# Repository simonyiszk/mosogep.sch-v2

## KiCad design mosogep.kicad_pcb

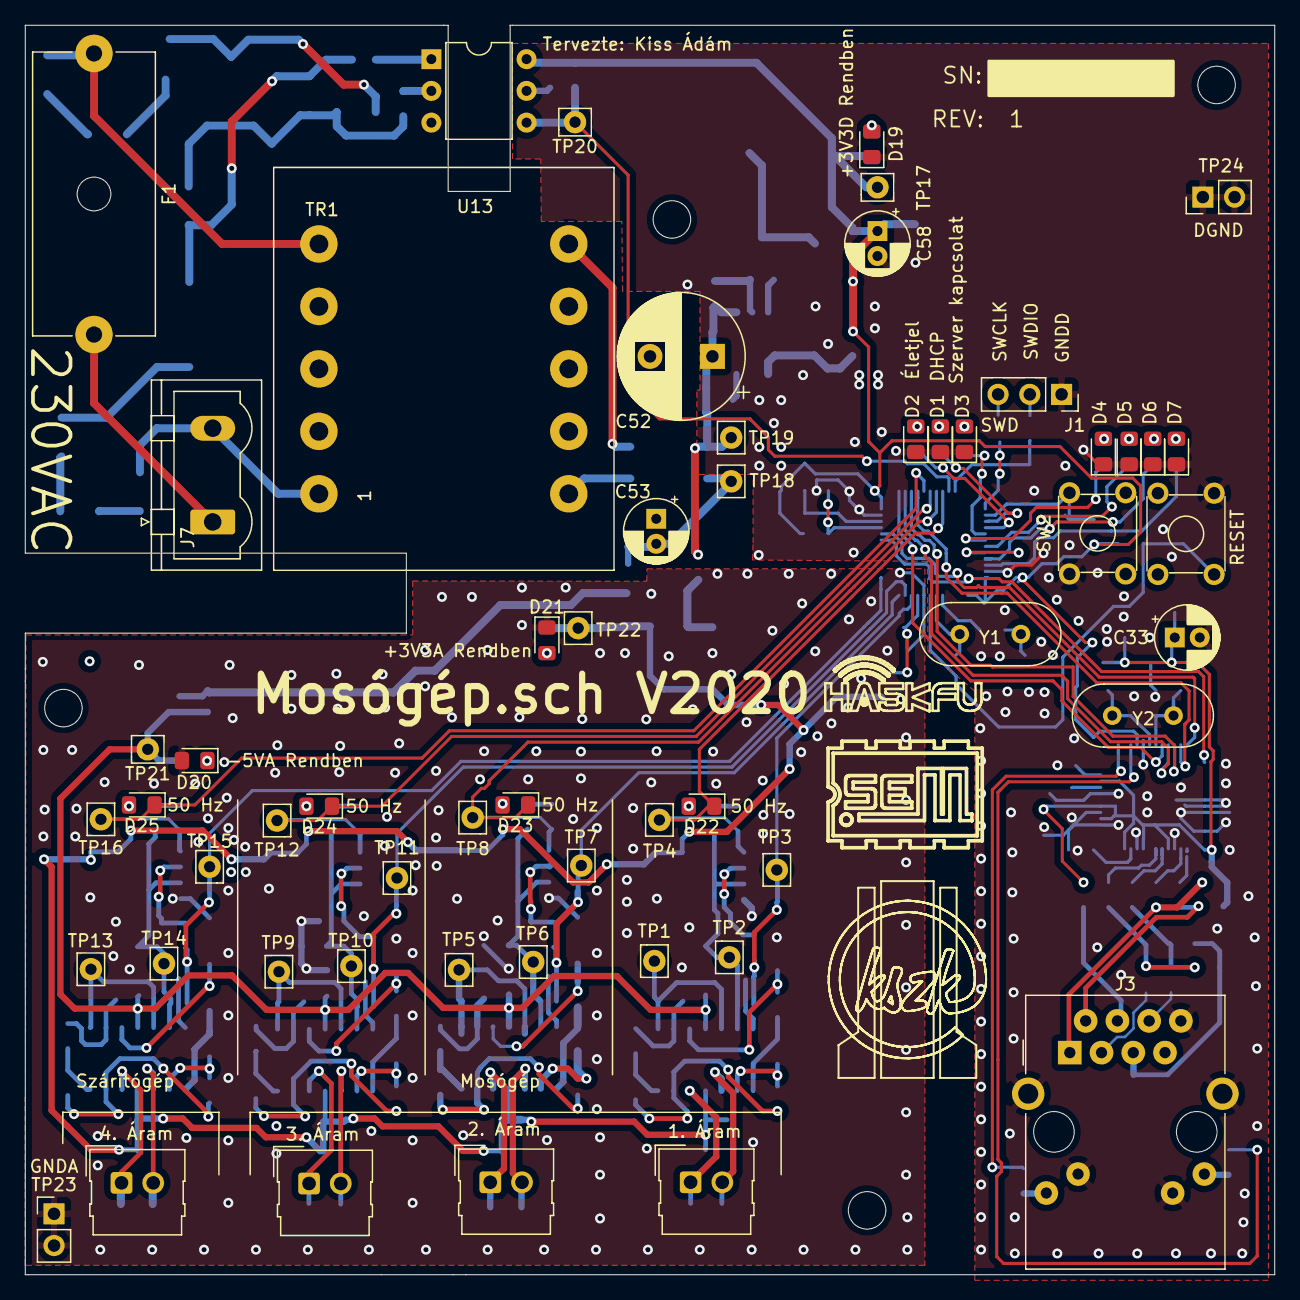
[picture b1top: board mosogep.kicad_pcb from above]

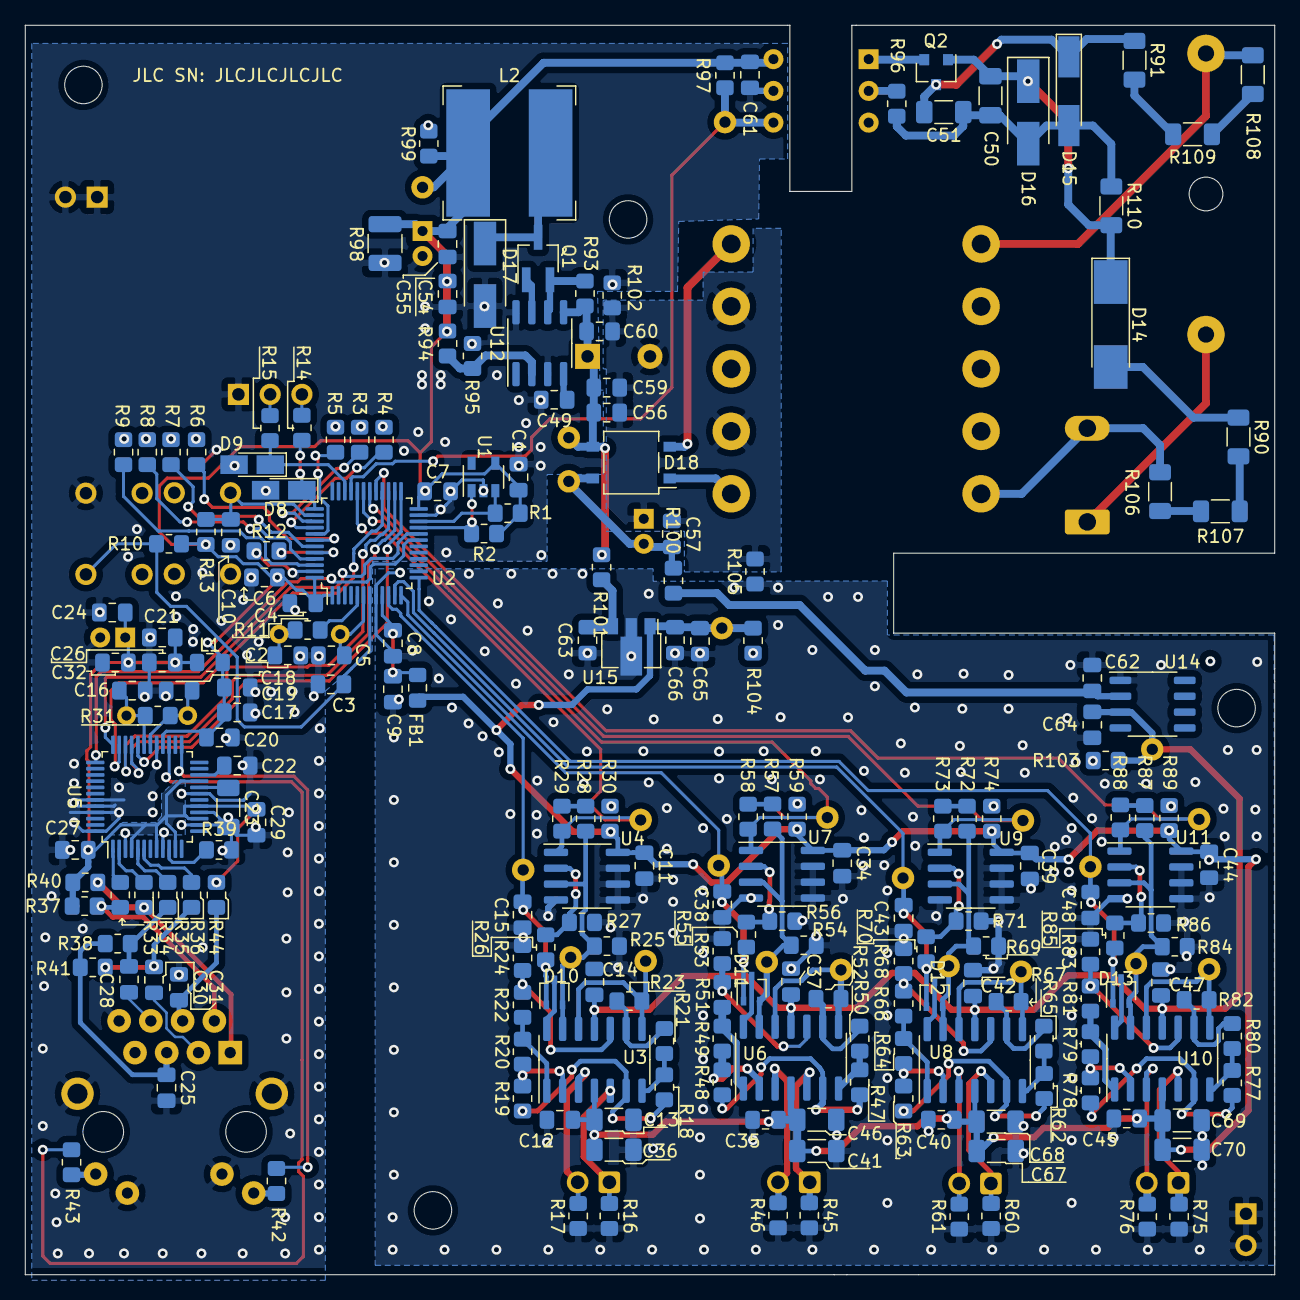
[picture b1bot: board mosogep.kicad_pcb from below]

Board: 2 copper layers, 100.0 x 100.0 mm, 264 parts (204 on the bottom side), 153 nets.

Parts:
C1, C4, C6, C7, C8, C11, C12, C14, C17, C19, C20, C21, C24, C26, C27, C29, C32, C34, C35, C37, C39, C40, C42, C44, C45, C47, C49, C54, C56, C57, C59, C60, C61, C62, C63: 100n; C_0805_2012Metric_Pad1.18x1.45mm_HandSolder
C2, C5: 20p; C_0805_2012Metric_Pad1.18x1.45mm_HandSolder
C3, C9, C10, C22, C25, C55, C65, C66: 10n; C_0805_2012Metric_Pad1.18x1.45mm_HandSolder
C13, C23, C36, C41, C46, C67, C68, C69, C70: 4u7; C_1206_3216Metric_Pad1.33x1.80mm_HandSolder
C15, C38, C43, C48: 1u; C_0805_2012Metric_Pad1.18x1.45mm_HandSolder
C16, C18: 18p; C_0805_2012Metric_Pad1.18x1.45mm_HandSolder
C28, C30: 6n8; C_0805_2012Metric_Pad1.18x1.45mm_HandSolder
C31: 22n; C_0805_2012Metric_Pad1.18x1.45mm_HandSolder
C33: 10u; CP_Radial_D5.0mm_P2.00mm
C50: 560p; C_1206_3216Metric_Pad1.33x1.80mm_HandSolder
C51: 330n; C_1206_3216Metric_Pad1.33x1.80mm_HandSolder
C52: 1000u; CP_Radial_D10.0mm_P5.00mm
C53: 100u; CP_Radial_D5.0mm_P2.00mm
C58: 47u low esr; CP_Radial_D5.0mm_P2.00mm
C64: C; C_0805_2012Metric_Pad1.18x1.45mm_HandSolder
D1, D2, D3, D4, D5, D6, D7, D19, D20, D21, D22, D23, D24, D25: LED; LED_0805_2012Metric_Pad1.15x1.40mm_HandSolder
D8, D9: PGB1010603MR; D_MicroMELF_Handsoldering
D10, D11, D12, D13: BAT54AW; SOT-323_SC-70
D14: bzd27c100; D_MELF_Handsoldering
D15: 5V6; D_MiniMELF_Handsoldering
D16: ll4148; D_SMA_Handsoldering
D17: ss14; D_SMA_Handsoldering
D18: MB6S; TO-269AA
F1: 100mA; Fuseholder_Cylinder-5x20mm_Schurter_0031_8201_Horizontal_Op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
FB1: HF70ACC575032-TL; L_0805_2012Metric_Pad1.15x1.40mm_HandSolder
H1, H2, H3, H4: MountingHole; MountingHole_3mm
J1: Programozó csati; PinSocket_1x03_P2.54mm_Vertical
J2, J4, J5, J6: AC1010; Molex_SL_171971-0002_1x02_P2.54mm_Vertical
J3: RB1-1D6B8K1A; RJ45_Amphenol_RJMG1BD3B8K1ANR
J7: line_in; PhoenixContact_GMSTBVA_2,5_2-G_1x02_P7.50mm_Vertical
L1: HF70ACC575032-TL; L_0805_2012Metric_Pad1.15x1.40mm_HandSolder
L2: 93-03-18; L_Bourns-SRN1060
Q1: yjl2301c; SOT-23W_Handsoldering
Q2: BC817; SOT-23
R1, R2, R10, R12, R13, R30, R37, R40, R59, R74, R89: 10k; R_0805_2012Metric_Pad1.20x1.40mm_HandSolder
R3, R4, R5, R6, R7, R8, R9, R42, R43, R99: 330; R_0805_2012Metric_Pad1.20x1.40mm_HandSolder
R11: 470; R_0805_2012Metric_Pad1.20x1.40mm_HandSolder
R14, R15, R44, R100, R101: 10; R_0805_2012Metric_Pad1.20x1.40mm_HandSolder
R16, R17, R38, R41, R45, R46, R60, R61, R75, R76: 50; R_0805_2012Metric_Pad1.20x1.40mm_HandSolder
R18, R20, R23, R24, R25, R47, R49, R52, R53, R54, R62, R64, R67, R68, R69, R77, R79, R82, R83, R84: 100k; R_0805_2012Metric_Pad1.20x1.40mm_HandSolder
R19, R21, R22, R48, R50, R51, R63, R65, R66, R78, R80, R81: 200k; R_0805_2012Metric_Pad1.20x1.40mm_HandSolder
R26, R27, R55, R56, R70, R71, R85, R86: 50k; R_0805_2012Metric_Pad1.20x1.40mm_HandSolder
R28, R29, R31, R57, R58, R72, R73, R87, R88: 1M; R_0805_2012Metric_Pad1.20x1.40mm_HandSolder
R33, R34, R35, R36, R93, R102, R105: 0; R_0805_2012Metric_Pad1.20x1.40mm_HandSolder
R39: 12.4k 1%; R_0805_2012Metric_Pad1.20x1.40mm_HandSolder
R90, R91, R106, R107, R108, R109: 82k; R_1206_3216Metric_Pad1.30x1.75mm_HandSolder
R94, R95, R103, R104: R; R_0805_2012Metric_Pad1.20x1.40mm_HandSolder
R96: 220; R_0805_2012Metric_Pad1.20x1.40mm_HandSolder
R97: 1k; R_0805_2012Metric_Pad1.20x1.40mm_HandSolder
R98: műterhelés; R_1210_3225Metric_Pad1.30x2.65mm_HandSolder
R110: 470k; R_1206_3216Metric_Pad1.30x1.75mm_HandSolder
SW1, SW2: SW_DIP_x01; SW_TH_Tactile_Omron_B3F-10xx
TP1, TP2, TP3, TP4, TP5, TP6, TP7, TP8, TP9, TP10, TP11, TP12, TP13, TP14, TP15, TP16, TP17, TP18, TP19, TP20, TP21, TP22: TestPoint; Pin_D0.9mm_L10.0mm_W2.4mm_FlatFork
TP23, TP24: TestPoint_2Pole; PinHeader_1x02_P2.54mm_Vertical
TR1: TEZ2.0-D-2; Transformer_CHK_EI30-2VA_Neutral
U1: 24AA02-OT; SOT-23-5
U2: STM32F030C6Tx; LQFP-48_7x7mm_P0.5mm
U3, U6, U8, U10: mc33204; SOIC-14_3.9x8.7mm_P1.27mm
U4, U7, U9, U11: LM393; SOIC-8_3.9x4.9mm_P1.27mm
U5: W5500; LQFP-48_7x7mm_P0.5mm
U12: max1649; SOIC-8_3.9x4.9mm_P1.27mm
U13: H11L1; DIP-6_W7.62mm
U14: L79L05_SOT89; SO-8_3.9x4.9mm_P1.27mm
U15: L78L33_SOT89; SOT-89-3
Y1: 8MHz; Crystal_HC18-U_Vertical
Y2: 25MHz; Crystal_HC18-U_Vertical

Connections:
0: C52.2, C53.1, C56.2, C57.1, C59.2, C60.2, R102.2, R105.2, TR1.7, TR1.9
+3.3VA: C11.1, C12.1, C13.1, C34.1, C35.1, C36.1, C39.1, C40.1, C41.1, C44.1, C45.1, C46.1, C65.1, C66.1, C67.1, C68.1, C69.1, C70.1, FB1.2, R30.1, R59.1, R74.1, R89.1, R104.1, TP22.1, U3.4, U4.8, U6.4, U7.8, U8.4, U9.8, U10.4, U11.8, U15.1
+3V3: C1.1, C4.1, C6.1, C7.1, C17.1, C19.1, C20.1, C54.1, C55.1, C58.1, C61.1, L1.2, L2.1, R1.1, R2.1, R10.1, R13.1, R94.1, R97.1, R98.1, R99.1, TP17.1, U1.4, U2.1, U2.24, U2.48, U5.28, U13.6
-3V3: C14.1, C37.1, C42.1, C47.1, C64.2, R103.2, TP21.1, U3.11, U6.11, U8.11, U10.11, U14.3
/ETH_INT: U2.20, U5.36
/I2C_CLK: R2.2, U1.1, U2.21
/I2C_DAT: R1.2, U1.3, U2.22
/MISO: U2.27, U5.34
/MOSI: U2.28, U5.35
/SCLK: U2.26, U5.33
/aram1: C15.1, D10.1, R26.1, TP3.1, U2.10
/aram2: C38.1, D11.1, R55.1, TP7.1, U2.12
/aram3: C43.1, D12.1, R70.1, TP11.1, U2.11
/aram4: C48.1, D13.1, R85.1, TP15.1, U2.13
/fazis_referencia: R97.2, TP20.1, U2.33, U13.4
/fazisdetektor1: D22.1, R29.1, TP4.1, U2.32, U4.1
/fazisdetektor2: D23.1, R58.1, TP8.1, U2.31, U7.1
/fazisdetektor3: D24.1, R73.1, TP12.1, U2.30, U9.1
/fazisdetektor4: D25.1, R88.1, TP16.1, U2.29, U11.1
/nCS: U2.25, U5.32
/swclk: D8.1, R14.2, U2.37
/swdio: D9.1, R15.2, U2.34
/w5500_reset: U2.19, U5.37
GNDA: C8.2, C9.2, C11.2, C12.2, C13.2, C14.2, C15.2, C34.2, C35.2, C36.2, C37.2, C38.2, C39.2, C40.2, C41.2, C42.2, C43.2, C44.2, C45.2, C46.2, C47.2, C48.2, C62.1, C63.2, C64.1, C65.2, C66.2, C67.2, C68.2, C69.2, C70.2, D20.2, D21.1, R16.2, R17.1, R24.1, R25.2, R27.2, R45.2, R46.1, R53.1, R54.2, R56.2, R60.2, R61.1, R68.1, R69.2, R71.2, R75.2, R76.1, R83.1, R84.2, R86.2, R105.1, TP23.1, TP23.2, U2.8, U4.4, U4.5, U4.6, U4.7, U7.4, U7.5, U7.6, U7.7, U9.4, U9.5, U9.6, U9.7, U11.4, U11.5, U11.6, U11.7, U14.1, U15.2
GNDD: C1.2, C2.2, C3.2, C4.2, C5.2, C6.2, C7.2, C10.2, C16.2, C17.2, C18.2, C19.2, C20.2, C21.2, C22.2, C23.2, C24.2, C25.2, C26.2, C27.2, C29.2, C31.2, C32.2, C33.2, C49.2, C54.2, C55.2, C58.2, C61.2, D1.1, D2.1, D3.1, D4.1, D5.1, D6.1, D7.1, D8.2, D9.2, D17.2, D19.1, J1.1, J3.13, J3.L2, J3.L3, J3.R8, R12.2, R39.2, R95.2, R98.2, R102.1, SW1.1, SW2.1, TP24.1, TP24.2, U1.2, U2.23, U2.47, U5.3, U5.9, U5.14, U5.16, U5.19, U5.29, U5.43, U5.44, U5.45, U5.48, U12.3, U12.8, U13.5
unnamed: C2.1, R11.1, Y1.1
unnamed: C3.1, R10.2, SW1.2, U2.7
unnamed: C5.1, U2.6, Y1.2
unnamed: C8.1, C9.1, FB1.1, U2.9
unnamed: C10.1, R13.2, SW2.2, U2.38
unnamed: C16.1, R31.2, U5.31, Y2.1
unnamed: C18.1, R31.1, U5.30, Y2.2
unnamed: C21.1, C24.1, C26.1, C27.1, C29.1, C32.1, C33.1, L1.1, R37.1, R40.1, R44.1, U5.4, U5.8, U5.11, U5.15, U5.17, U5.21
unnamed: C22.1, U5.22
unnamed: C23.1, U5.20
unnamed: C25.1, J3.R5, R38.2, R41.2
unnamed: C28.1, J3.R6
unnamed: C28.2, R35.1, R38.1
unnamed: C30.1, J3.R3
unnamed: C30.2, R36.1, R41.1
unnamed: C31.1, J3.R4, R44.2
unnamed: C49.1, U12.4
unnamed: C50.1, C51.1, D15.2, D16.2, R96.2, R110.1
unnamed: C50.2, D14.1, D16.1, Q2.1, R110.2
unnamed: C51.2, D15.1, Q2.3, R91.1
unnamed: C52.1, C56.1, C59.1, C60.1, D18.3, R93.1, R101.2, TP19.1, U12.5
unnamed: C53.2, C57.2, D18.4, R100.2, TP18.1
unnamed: C62.2, R100.1, U14.2
unnamed: C63.1, R101.1, U15.3
unnamed: D1.2, R3.2
unnamed: D2.2, R4.2
unnamed: D3.2, R5.2
unnamed: D4.2, R6.2
unnamed: D5.2, R7.2
unnamed: D6.2, R8.2
unnamed: D7.2, R9.2
unnamed: D10.2, R25.1, R28.1, TP2.1, U3.13, U4.3
unnamed: D10.3, U3.14
unnamed: D11.2, R54.1, R57.1, TP6.1, U6.13, U7.3
unnamed: D11.3, U6.14
unnamed: D12.2, R69.1, R72.1, TP10.1, U8.13, U9.3
unnamed: D12.3, U8.14
unnamed: D13.2, R84.1, R87.1, TP14.1, U10.13, U11.3
unnamed: D13.3, U10.14
unnamed: D14.2, R90.1
unnamed: D17.1, L2.2, Q1.3
unnamed: D18.1, TR1.10
unnamed: D18.2, TR1.6
unnamed: D19.2, R99.2
unnamed: D20.1, R103.1
unnamed: D21.2, R104.2
unnamed: D22.2, R30.2
unnamed: D23.2, R59.2
unnamed: D24.2, R74.2
unnamed: D25.2, R89.2
unnamed: F1.1, R108.1, TR1.5
unnamed: F1.2, J7.1
unnamed: J1.2, R15.1
unnamed: J1.3, R14.1
unnamed: J2.1, R16.1, U3.5
unnamed: J2.2, R17.2, U3.3
unnamed: J3.L1, R43.1
unnamed: J3.L4, R42.1
unnamed: J3.R1, R34.1, R40.2
unnamed: J3.R2, R33.1, R37.2
unnamed: J4.1, R45.1, U6.5
unnamed: J4.2, R46.2, U6.3
unnamed: J5.1, R60.1, U8.5
unnamed: J5.2, R61.2, U8.3
unnamed: J6.1, R75.1, U10.5
unnamed: J6.2, R76.2, U10.3
unnamed: J7.2, R106.1, TR1.1
unnamed: Q1.1, U12.7
unnamed: Q1.2, R93.2, U12.6
unnamed: Q2.2, U13.1
unnamed: R3.1, U2.39
unnamed: R4.1, U2.40
unnamed: R5.1, U2.41
unnamed: R6.1, U2.42
unnamed: R7.1, U2.43
unnamed: R8.1, U2.45
unnamed: R9.1, U2.46
unnamed: R11.2, U2.5
unnamed: R12.1, U2.44
unnamed: R18.1, R21.2, U3.7
unnamed: R18.2, R19.1, U3.6
unnamed: R19.2, R20.1, U3.2
unnamed: R20.2, R22.2, U3.1
unnamed: R21.1, R23.2, U3.9
unnamed: R22.1, R24.2, U3.10
unnamed: R23.1, TP1.1, U3.8, U3.12
unnamed: R26.2, R27.1, U4.2
unnamed: R28.2, R29.2
unnamed: R33.2, U5.1
unnamed: R34.2, U5.2
unnamed: R35.2, U5.5
unnamed: R36.2, U5.6
unnamed: R39.1, U5.10
unnamed: R42.2, U5.25
unnamed: R43.2, U5.27
unnamed: R47.1, R50.2, U6.7
unnamed: R47.2, R48.1, U6.6
unnamed: R48.2, R49.1, U6.2
unnamed: R49.2, R51.2, U6.1
unnamed: R50.1, R52.2, U6.9
unnamed: R51.1, R53.2, U6.10
unnamed: R52.1, TP5.1, U6.8, U6.12
unnamed: R55.2, R56.1, U7.2
unnamed: R57.2, R58.2
unnamed: R62.1, R65.2, U8.7
unnamed: R62.2, R63.1, U8.6
unnamed: R63.2, R64.1, U8.2
unnamed: R64.2, R66.2, U8.1
unnamed: R65.1, R67.2, U8.9
unnamed: R66.1, R68.2, U8.10
unnamed: R67.1, TP9.1, U8.8, U8.12
unnamed: R70.2, R71.1, U9.2
unnamed: R72.2, R73.2
unnamed: R77.1, R80.2, U10.7
unnamed: R77.2, R78.1, U10.6
unnamed: R78.2, R79.1, U10.2
unnamed: R79.2, R81.2, U10.1
unnamed: R80.1, R82.2, U10.9
unnamed: R81.1, R83.2, U10.10
unnamed: R82.1, TP13.1, U10.8, U10.12
unnamed: R85.2, R86.1, U11.2
unnamed: R87.2, R88.2
unnamed: R94.2, R95.1, U12.2
unnamed: R96.1, U13.2
unnamed: R106.2, R107.1
unnamed: R90.2, R107.2
unnamed: R108.2, R109.1
unnamed: R91.2, R109.2

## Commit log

2020-09-21 Some progress
2020-09-21 Improvements
2020-09-21 correct op amp type to rail-to-rail
2020-09-22 Tápegység külön lap + fázisméréshez áramkörök
2020-09-22 Testpoints + ground connections
2020-10-10 3v3 finished
2020-10-10 front silk
2020-10-11 Bottom silk
2020-10-13 Krisztián megjegyzései 1
2022-05-04 updated L2 value
2022-06-29 ellenállás érték változása könnyebb beszer miatt: 50R -> 51R, 50k -> 51k
